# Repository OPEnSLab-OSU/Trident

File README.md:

# Trident

Multiplexor-based variable vertical resistance tomography (VVRT) system with point measurements of electrical conductivity, temperature, and pressure.

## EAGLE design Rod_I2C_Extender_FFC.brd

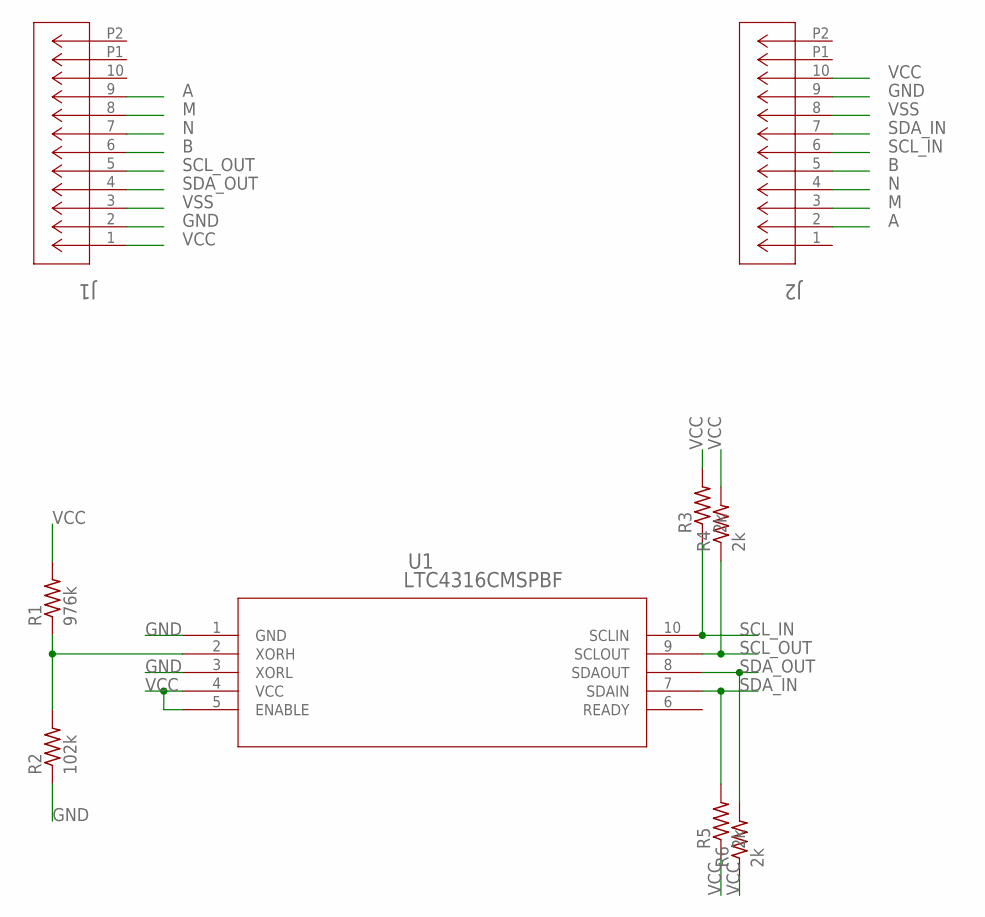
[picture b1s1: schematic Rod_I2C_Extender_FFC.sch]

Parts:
J1, J2: 522711079; CON_522711079_MOL
R1: 976k; R0603
R2: 102k; R0603
R3, R4, R5, R6: 2k; R0603
U1: LTC4316CMSPBF; MSOP-10_MS

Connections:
A: J1.9, J2.2
B: J1.6, J2.5
GND: J1.2, J2.9, R2.1, U1.1 (GND), U1.3 (XORL)
M: J1.8, J2.3
N: J1.7, J2.4
unnamed: R1.1, R2.2, U1.2 (XORH)
SCL_IN: J2.6, R3.1, U1.10 (SCLIN)
SCL_OUT: J1.5, R4.1, U1.9 (SCLOUT)
SDA_IN: J2.7, R5.2, U1.7 (SDAIN)
SDA_OUT: J1.4, R6.2, U1.8 (SDAOUT)
VCC: J1.1, J2.10, R1.2, R3.2, R4.2, R5.1, R6.1, U1.4 (VCC), U1.5 (ENABLE)
VSS: J1.3, J2.8

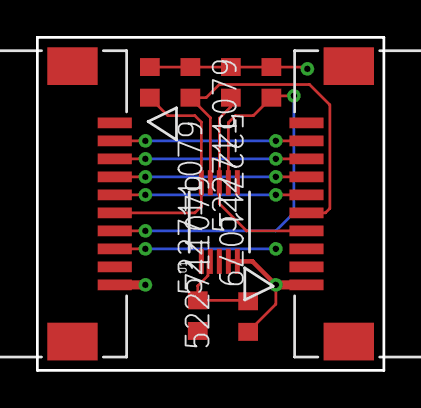
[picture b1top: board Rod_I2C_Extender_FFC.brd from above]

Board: 2 copper layers, 19.2 x 18.5 mm, 9 parts (0 on the bottom side), 12 nets.

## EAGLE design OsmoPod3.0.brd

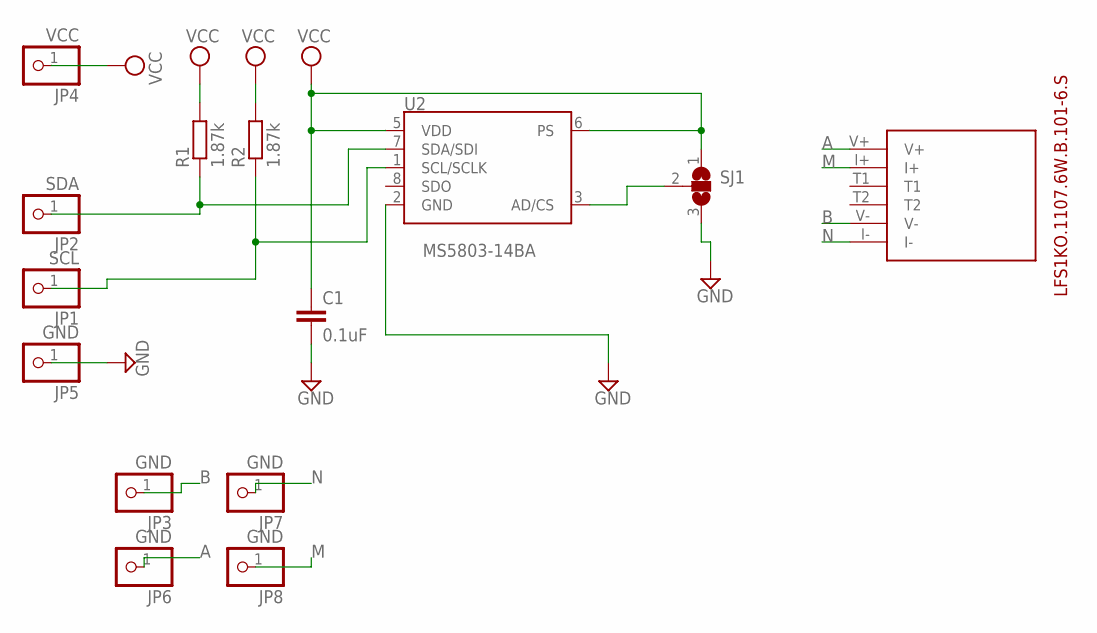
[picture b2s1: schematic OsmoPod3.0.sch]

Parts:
C1: 0.1uF; C0805
JP1: SCL; 1X01
JP2: SDA; 1X01
JP3, JP5, JP6, JP7, JP8: GND; 1X01
JP4: VCC; 1X01
R1, R2: 1.87k; R0805
SJ1: SJ2W; SJ_2
U2: MS5803-14BA; MS5803
U$1: LFS1107_6W

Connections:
A: JP6.1, U$1.V+
B: JP3.1, U$1.V-
CSB: SJ1.2, U2.3 (AD/CS)
GND: C1.2, JP5.1, SJ1.3, U2.2 (GND)
M: JP8.1, U$1.I+
N: JP7.1, U$1.I-
SCL: JP1.1, R2.1, U2.1 (SCL/SCLK)
SDA: JP2.1, R1.1, U2.7 (SDA/SDI)
VCC: C1.1, JP4.1, R1.2, R2.2, SJ1.1, U2.5 (VDD), U2.6 (PS)

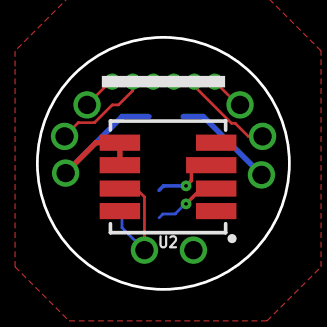
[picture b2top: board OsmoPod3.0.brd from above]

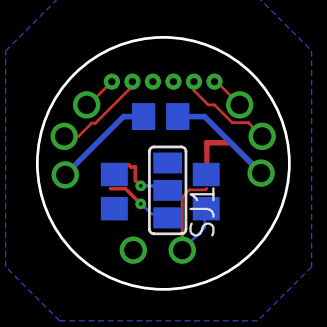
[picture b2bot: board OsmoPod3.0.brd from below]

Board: 2 copper layers, 14.0 x 14.0 mm, 14 parts (4 on the bottom side), 9 nets.

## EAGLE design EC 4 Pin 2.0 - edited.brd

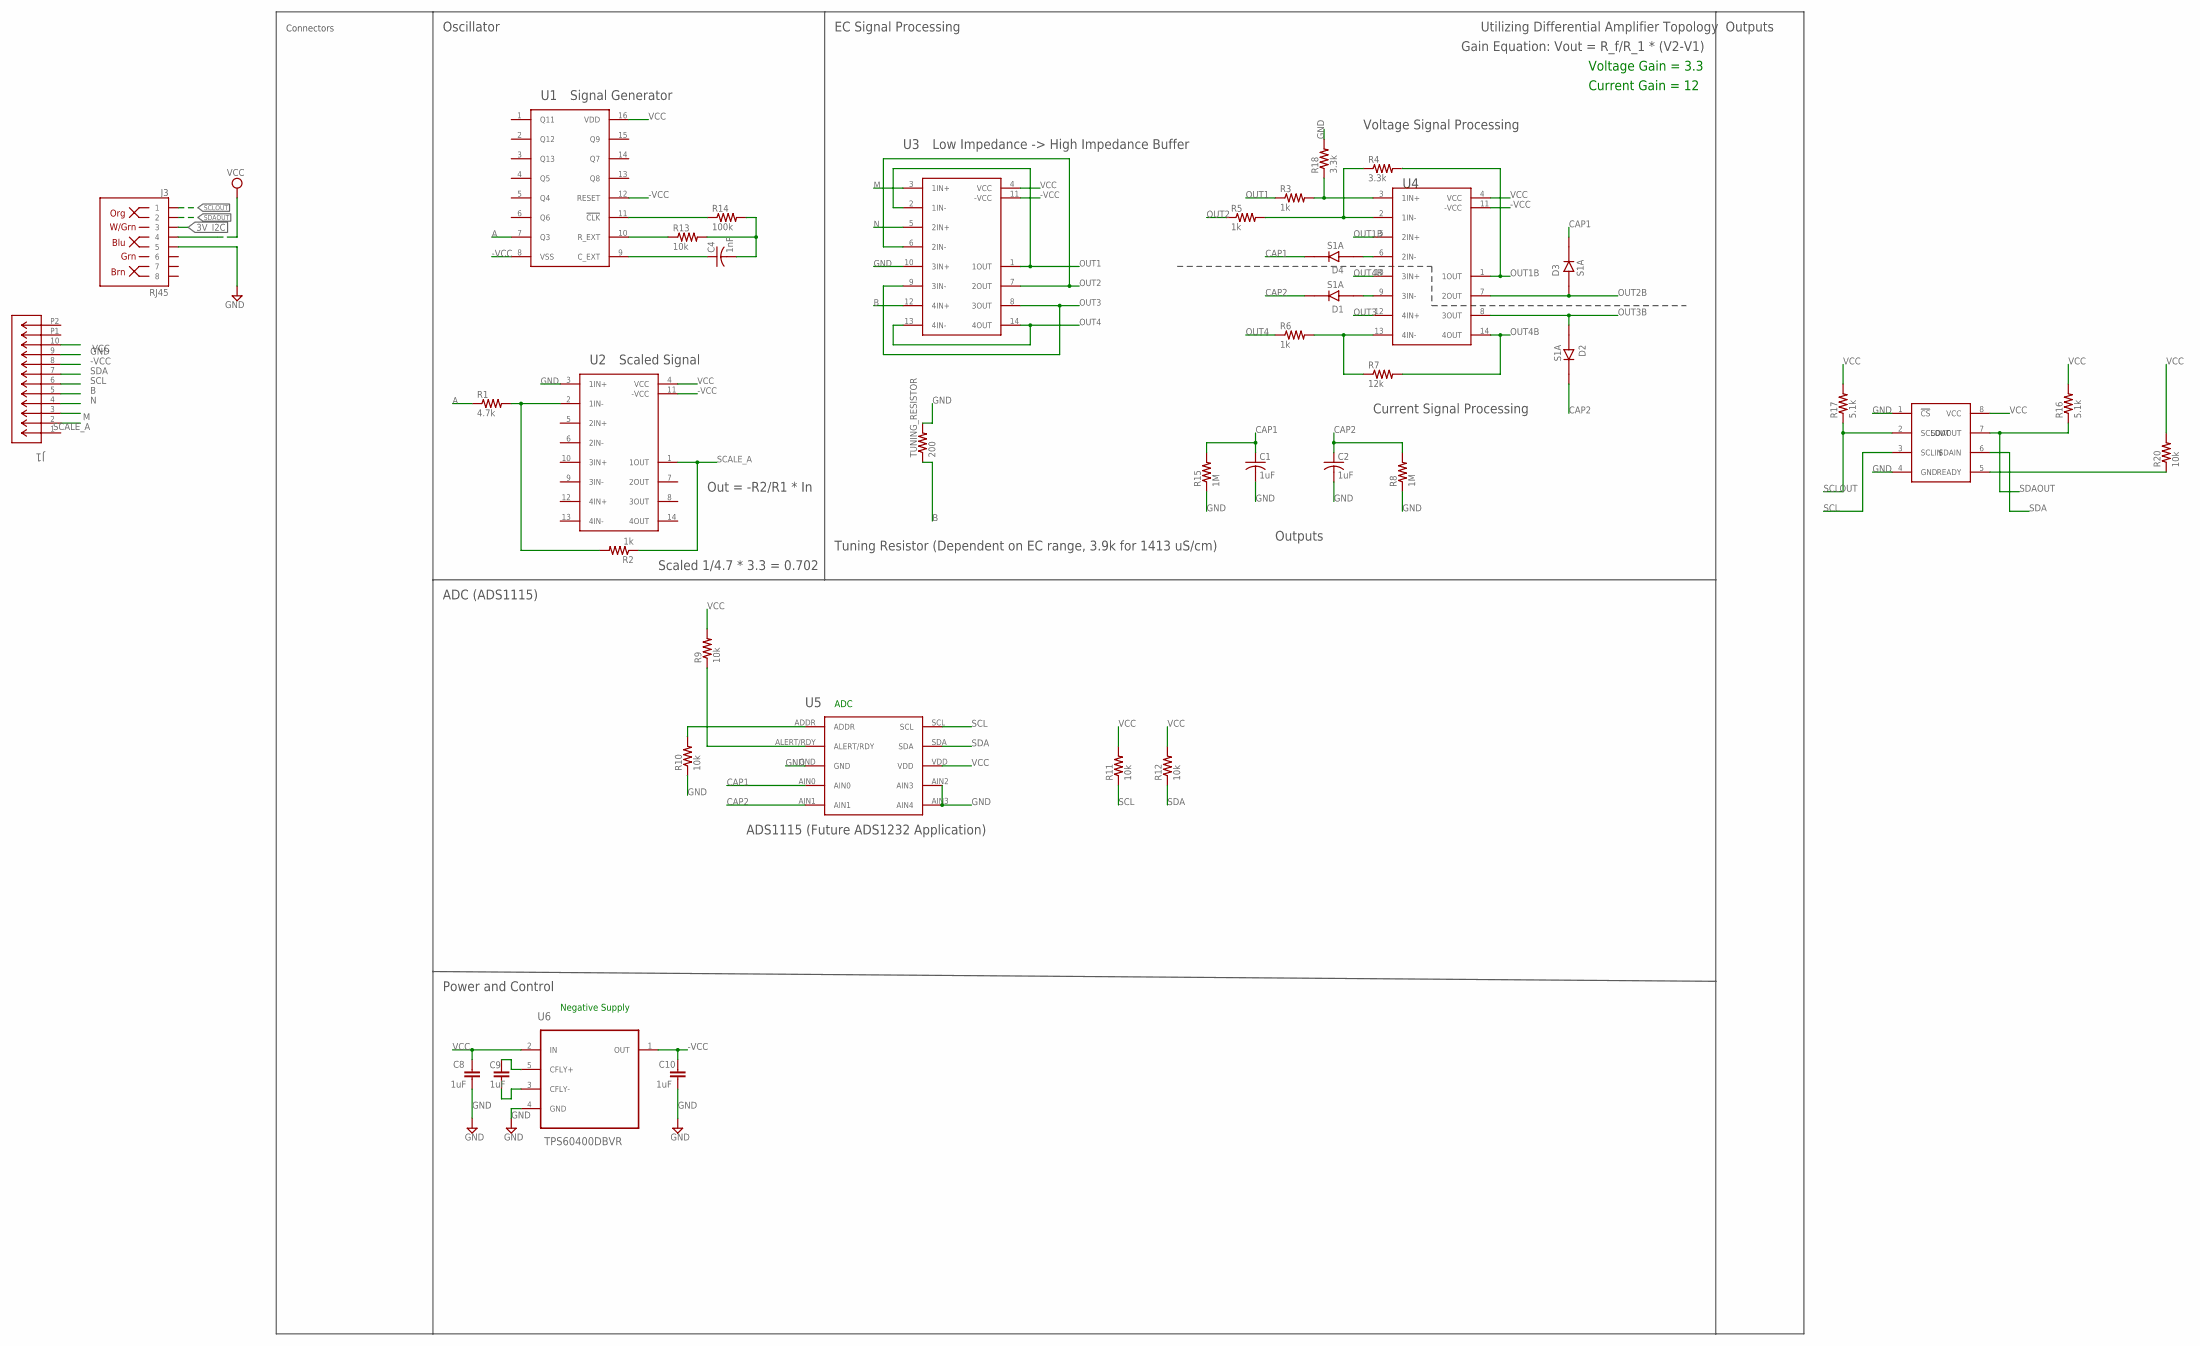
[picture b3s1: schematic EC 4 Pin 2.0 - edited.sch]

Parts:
C1, C2: 1uF; C025-024X044
C4: 1nF; C1206
C8, C9, C10: 1uF; C1206
D1, D2, D3, D4: S1A; DIOM5227X270N
J1: 522711079; CON_522711079_MOL
J3: RJ45; RJ45-8
R1: 4.7k; M1206
R2, R3, R5, R6: 1k; M1206
R4, R18: 3.3k; M1206
R7: 12k; M1206
R8, R15: 1M; M1206
R9, R10, R11, R12, R13, R20: 10k; M1206
R14: 100k; M1206
R16, R17: 5.1k; M1206
TUNING_RESISTOR: 200; M1206
U1: CD4060BPWR
U2, U3, U4: TL074CPWR; LT074CPWR
U5: ADS1115
U6: TPS60400DBVR; SOT95P280X145-5N
U$1: LTC4301

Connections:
3V_I2C: J3.3
-VCC: C10.2, J1.8, U1.8 (VSS), U1.12 (RESET), U2.11 (-VCC), U3.11 (-VCC), U4.11 (-VCC), U6.1 (OUT)
A: R1.1, U1.7 (Q3)
B: J1.5, TUNING_RESISTOR.1, U3.12 (4IN+)
CAP1: C1.1, D3.1 (C), D4.1 (C), R15.2, U5.AIN0
CAP2: C2.1, D1.1 (C), D2.1 (C), R8.2, U5.AIN1
GND: C1.2, C2.2, C8.1, C10.1, J1.9, J3.5, R8.1, R10.1, R15.1, R18.2, TUNING_RESISTOR.2, U2.3 (1IN+), U3.10 (3IN+), U5.AIN2 (AIN3), U5.AIN3 (AIN4), U5.GND, U6.4 (GND), U$1.1 (!CS), U$1.4 (GND)
M: J1.3, U3.3 (1IN+)
N: J1.4, U3.5 (2IN+)
unnamed: R3.2, R18.1, U4.3 (1IN+)
unnamed: R4.1, R5.2, U4.2 (1IN-)
unnamed: R1.2, R2.2, U2.2 (1IN-)
unnamed: D4.2 (A), U4.6 (2IN-)
unnamed: R6.2, R7.1, U4.13 (4IN-)
unnamed: D1.2 (A), U4.9 (3IN-)
unnamed: C4.1, U1.9 (C_EXT)
unnamed: R13.1, U1.10 (R_EXT)
unnamed: R14.1, U1.11 (!CLK)
unnamed: R10.2, U5.ADDR
unnamed: R9.1, U5.ALERT/RDY
unnamed: R20.1, U$1.5 (READY)
unnamed: C4.2, R13.2, R14.2
unnamed: C9.2, U6.5 (CFLY+)
unnamed: C9.1, U6.3 (CFLY-)
OUT1: R3.1, U3.1 (1OUT), U3.2 (1IN-)
OUT1B: R4.2, U4.1 (1OUT), U4.5 (2IN+)
OUT2: R5.1, U3.6 (2IN-), U3.7 (2OUT)
OUT2B: D3.2 (A), U4.7 (2OUT)
OUT3: U3.8 (3OUT), U3.9 (3IN-), U4.12 (4IN+)
OUT3B: D2.2 (A), U4.8 (3OUT)
OUT4: R6.1, U3.13 (4IN-), U3.14 (4OUT)
OUT4B: R7.2, U4.10 (3IN+), U4.14 (4OUT)
SCALE_A: J1.2, R2.1, U2.1 (1OUT)
SCL: J1.6, R11.1, U5.SCL, U$1.3 (SCLIN)
SCLOUT: J3.1, R17.1, U$1.2 (SCLOUT)
SDA: J1.7, R12.1, U5.SDA, U$1.6 (SDAIN)
SDAOUT: J3.2, R16.1, U$1.7 (SDAOUT)
VCC: C8.2, J1.10, J3.4, R9.2, R11.2, R12.2, R16.2, R17.2, R20.2, U1.16 (VDD), U2.4 (VCC), U3.4 (VCC), U4.4 (VCC), U5.VDD, U6.2 (IN), U$1.8 (VCC)

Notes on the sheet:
Oscillator
ADC (ADS1115)
Outputs
Power and Control
Negative Supply
ADC
Connectors
EC Signal Processing
Signal Generator
Scaled Signal
Out = -R2/R1 * In
Scaled 1/4.7 * 3.3 = 0.702
Low Impedance -> High Impedance Buffer
Voltage Signal Processing
Current Signal Processing
Tuning Resistor (Dependent on EC range, 3.9k for 1413 uS/cm)
Utilizing Differential Amplifier Topology
Gain Equation: Vout = R_f/R_1 * (V2-V1)
ADS1115 (Future ADS1232 Application)
Voltage Gain = 3.3
Current Gain = 12

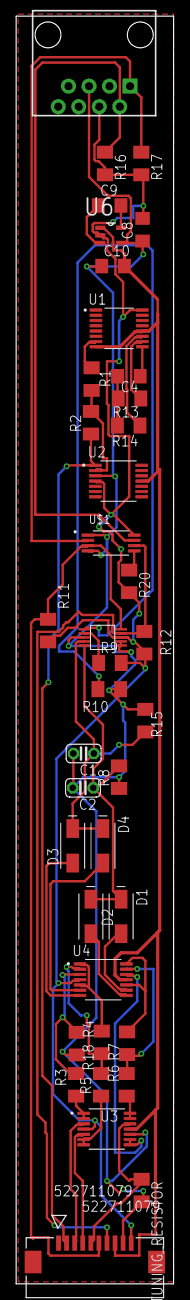
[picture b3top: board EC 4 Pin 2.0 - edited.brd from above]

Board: 2 copper layers, 19.5 x 157.0 mm, 39 parts (0 on the bottom side), 37 nets.

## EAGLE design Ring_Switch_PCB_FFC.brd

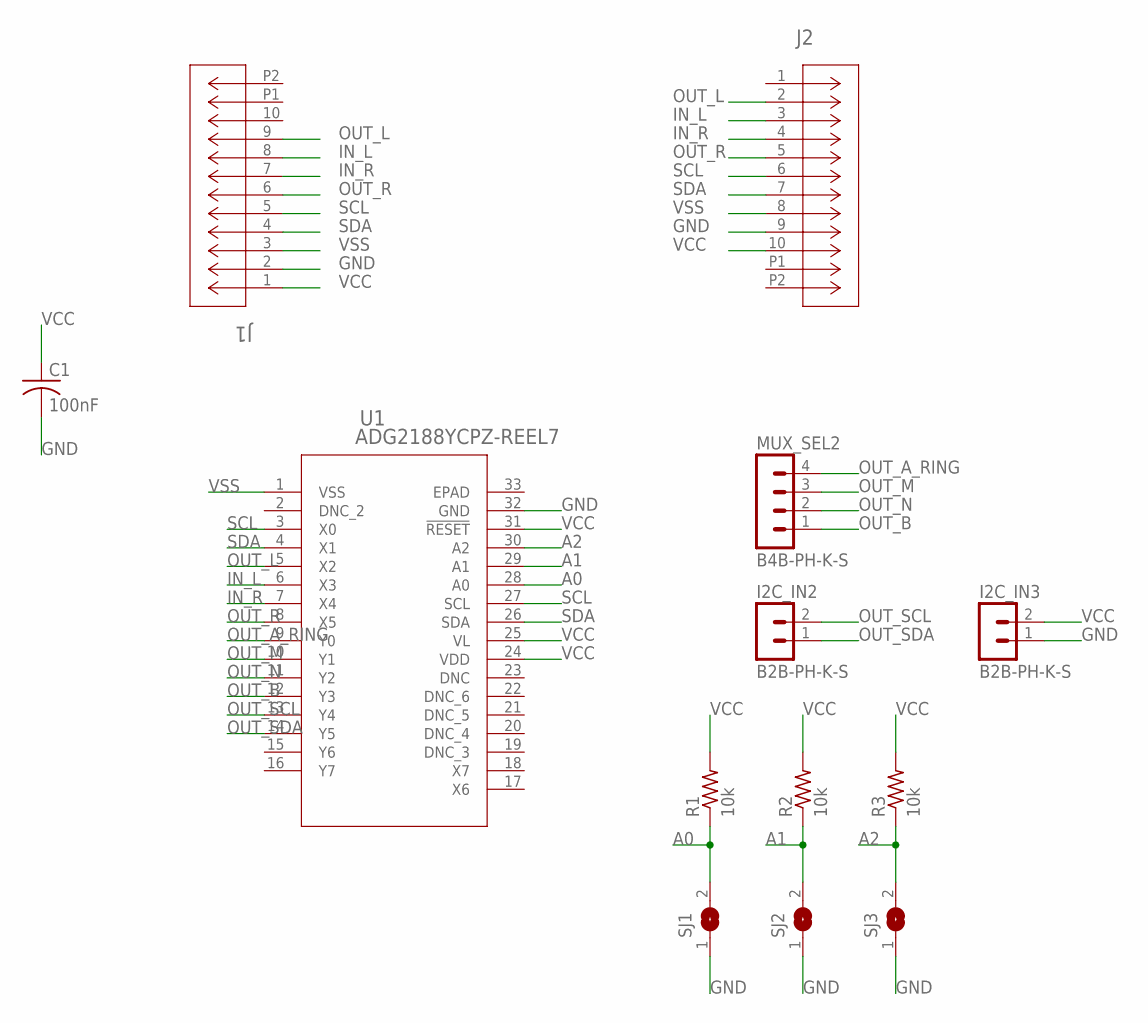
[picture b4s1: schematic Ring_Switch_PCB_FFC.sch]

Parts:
C1: 100nF; C0603
I2C_IN2, I2C_IN3: B2B-PH-K-S
J1, J2: 522711079; CON_522711079_MOL
MUX_SEL2: B4B-PH-K-S
R1, R2, R3: 10k; R0603
SJ1, SJ2, SJ3: SJ
U1: ADG2188YCPZ-REEL7; CP_32_7_ADI

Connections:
A0: R1.1, SJ1.2, U1.28 (A0)
A1: R2.1, SJ2.2, U1.29 (A1)
A2: R3.1, SJ3.2, U1.30 (A2)
GND: C1.2, I2C_IN3.1, J1.2, J2.9, SJ1.1, SJ2.1, SJ3.1, U1.32 (GND)
IN_L: J1.8, J2.3, U1.6 (X3)
IN_R: J1.7, J2.4, U1.7 (X4)
OUT_A_RING: MUX_SEL2.4, U1.9 (Y0)
OUT_B: MUX_SEL2.1, U1.12 (Y3)
OUT_L: J1.9, J2.2, U1.5 (X2)
OUT_M: MUX_SEL2.3, U1.10 (Y1)
OUT_N: MUX_SEL2.2, U1.11 (Y2)
OUT_R: J1.6, J2.5, U1.8 (X5)
OUT_SCL: I2C_IN2.2, U1.13 (Y4)
OUT_SDA: I2C_IN2.1, U1.14 (Y5)
SCL: J1.5, J2.6, U1.3 (X0), U1.27 (SCL)
SDA: J1.4, J2.7, U1.4 (X1), U1.26 (SDA)
VCC: C1.1, I2C_IN3.2, J1.1, J2.10, R1.2, R2.2, R3.2, U1.24 (VDD), U1.25 (VL), U1.31 (!RESET)
VSS: J1.3, J2.8, U1.1 (VSS)

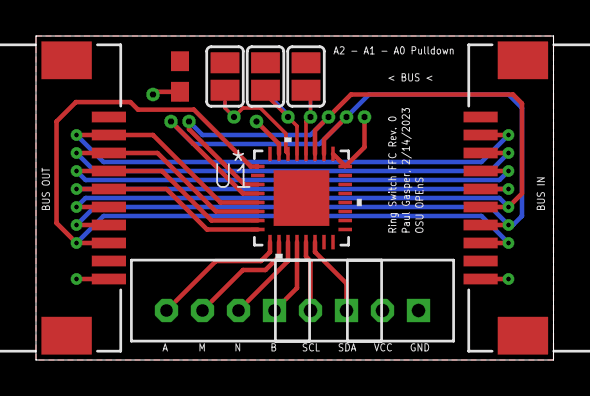
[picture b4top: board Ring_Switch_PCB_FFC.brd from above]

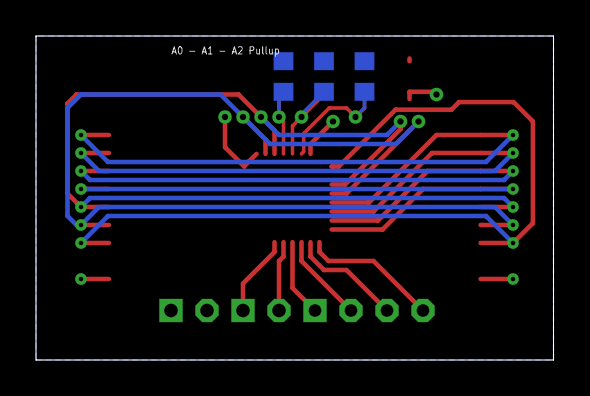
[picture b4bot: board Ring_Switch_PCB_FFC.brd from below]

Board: 2 copper layers, 28.8 x 18.0 mm, 13 parts (3 on the bottom side), 18 nets.

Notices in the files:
parts and their libraries:
SparkFun-Connectors: Licensing: Creative Commons ShareAlike 4.0 International - https://creativecommons.org/licenses/by-sa/4.0
COPYRIGHT: Copyright (C) 2023 Ultra Librarian. All rights reserved.
COPYRIGHT: Copyright (C) 2016 Accelerated Designs. All rights reserved
